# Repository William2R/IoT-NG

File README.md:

<h1 align="center">IndustrialSense</h1>
<p align="center">
  
  &nbsp; &nbsp; &nbsp; &nbsp;
  
</p>

***

## SPECIFICATIONS
| Parameter | Value | 
| --- | --- |
| **MCU** | ESP32-S3 |
| **LoRa Module** | Ra-01SH (Semtech SX1262) |
| **External Connectivity** | RS-485 / I2C / UART |
| **Expansion Support** | LTE A7680C (External Module via Headers) |
| **Dimensions** | 46.9 × 90.0 mm |

***

## DIRECTORY STRUCTURE

    .
    ├─ Computations       # Misc calculations
    ├─ HTML               # HTML files for generated webpage
    ├─ Images             # Pictures and renders
    │
    ├─ kibot_resources    # External resources for KiBot
    │  ├─ colors          # Color theme for KiCad
    │  ├─ fonts           # Fonts used in the project
    │  ├─ scripts         # External scripts used with KiBot
    │  └─ templates       # Templates for KiBot generated reports
    │
    ├─ kibot_yaml         # KiBot YAML config files
    ├─ KiRI               # KiRI (PCB diff viewer) files
    │
    ├─ lib                # KiCad footprint and symbol libraries
    │  ├─ 3d_models       # Component 3D models
    │  ├─ lib_fp          # Footprint libraries
    │  └─ lib_sym         # Symbol libraries
    │
    ├─ Logos              # Logos
    │
    ├─ Manufacturing      # Assembly and fabrication documents
    │  ├─ Assembly        # Assembly documents (BoM, pos, notes)
    │  │
    │  └─ Fabrication     # Fabrication documents (ZIP, notes)
    │     ├─ Drill Tables # CSV drill tables
    │     └─ Gerbers      # Gerbers
    │
    ├─ Report             # Reports for ERC/DRC
    ├─ Schematic          # PDF of schematic
    ├─ Templates          # Title block templates
    ├─ Testing
    │  └─ Testpoints      # Testpoints tables      
    │
    └─ Variants           # Outputs for assembly variants

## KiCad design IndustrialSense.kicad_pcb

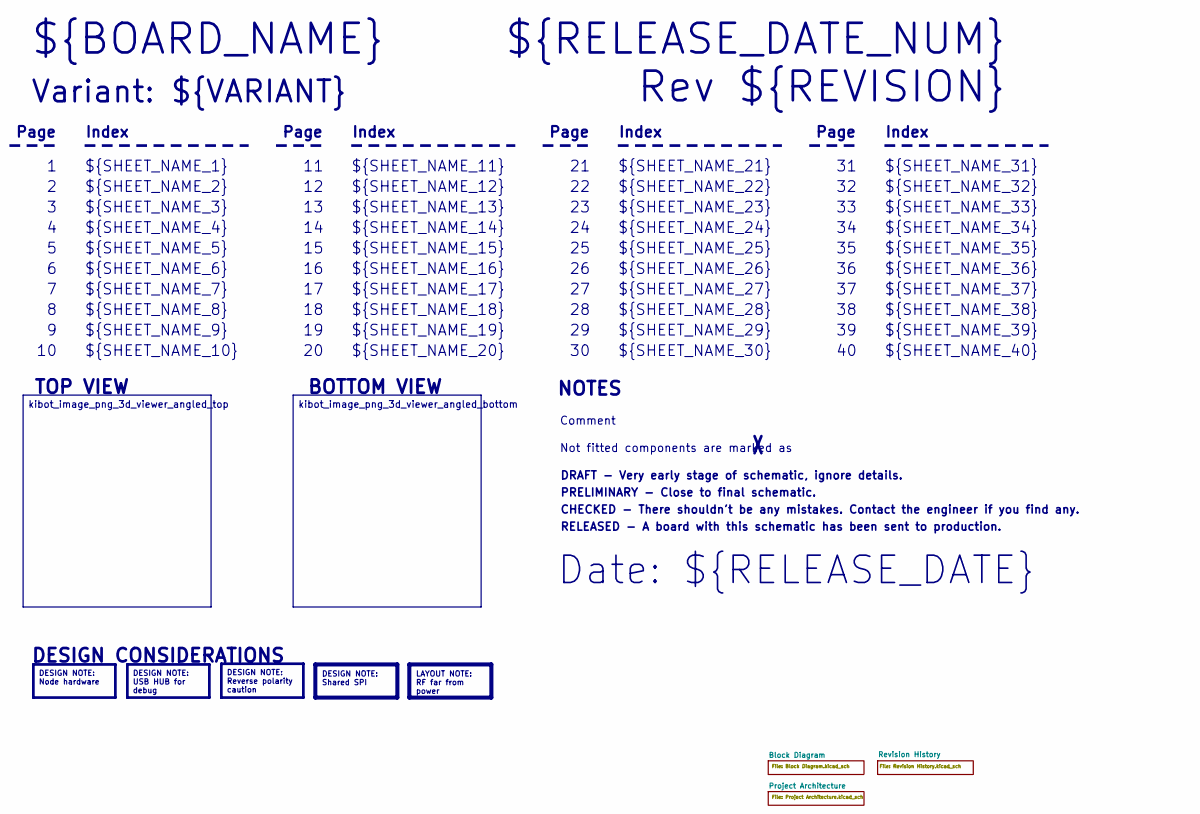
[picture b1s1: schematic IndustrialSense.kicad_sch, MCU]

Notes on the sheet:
Variant: ${VARIANT}
RELEASED - A board with this schematic has been sent to production.
${SHEET_NAME_24}
Index
Page
PRELIMINARY - Close to final schematic.
${SHEET_NAME_22}
DRAFT - Very early stage of schematic, ignore details.
${SHEET_NAME_12}
${SHEET_NAME_8}
${SHEET_NAME_2}
${SHEET_NAME_5}
${SHEET_NAME_20}
${SHEET_NAME_23}
${RELEASE_DATE_NUM}
${SHEET_NAME_35}
Not fitted components are marked as
${SHEET_NAME_11}
${SHEET_NAME_6}
${SHEET_NAME_37}
${SHEET_NAME_26}
${SHEET_NAME_36}
Rev ${REVISION}
${SHEET_NAME_15}
CHECKED - There shouldn't be any mistakes. Contact the engineer if you find any.
BOTTOM VIEW
${SHEET_NAME_14}
${SHEET_NAME_21}
${SHEET_NAME_17}
${SHEET_NAME_18}
Date: ${RELEASE_DATE}
${SHEET_NAME_7}
${SHEET_NAME_31}
${BOARD_NAME}
NOTES
${SHEET_NAME_40}
${SHEET_NAME_39}
${SHEET_NAME_32}
${SHEET_NAME_1}
${SHEET_NAME_9}

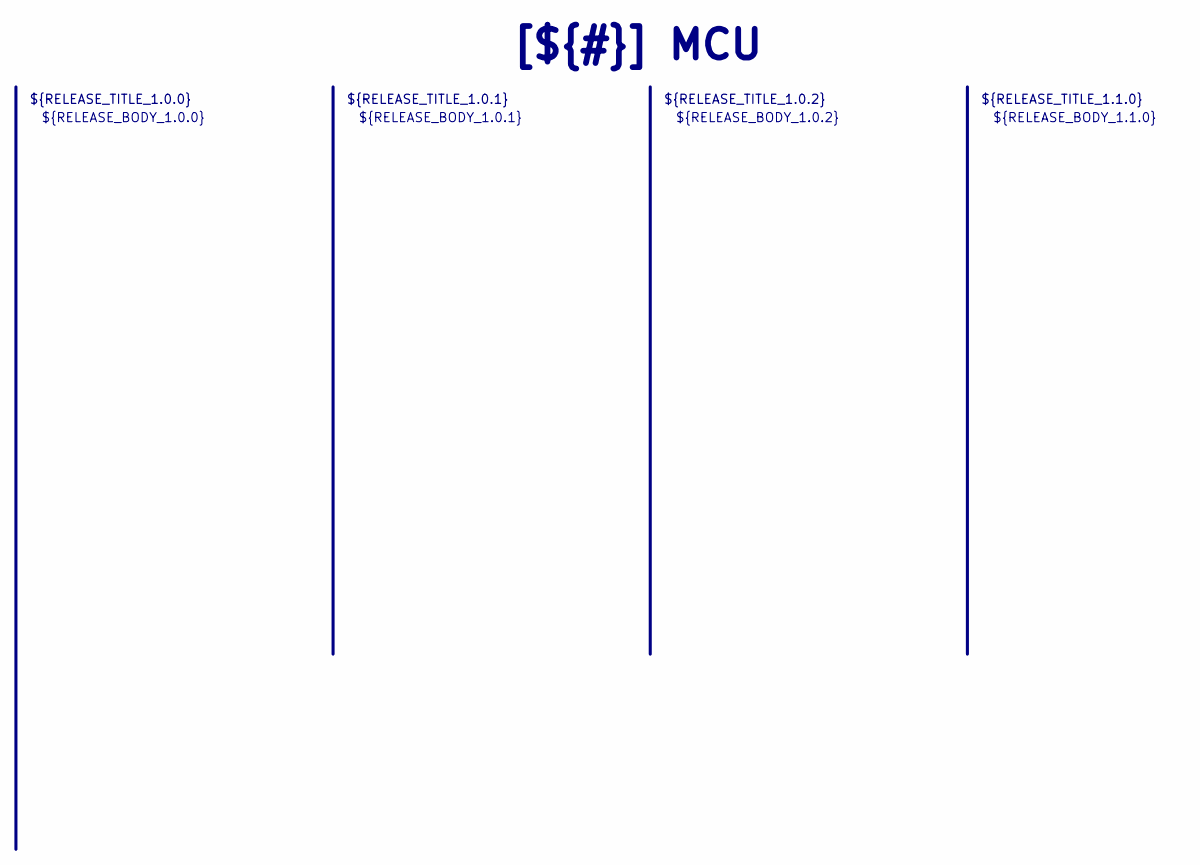
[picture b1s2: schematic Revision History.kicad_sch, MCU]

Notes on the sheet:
${RELEASE_BODY_1.1.0}
[${#}] ${TITLE}
${RELEASE_BODY_1.0.0}
${RELEASE_TITLE_1.0.2}
${RELEASE_BODY_1.0.2}
${RELEASE_BODY_1.0.1}
${RELEASE_TITLE_1.0.0}
${RELEASE_TITLE_1.0.1}
${RELEASE_TITLE_1.1.0}

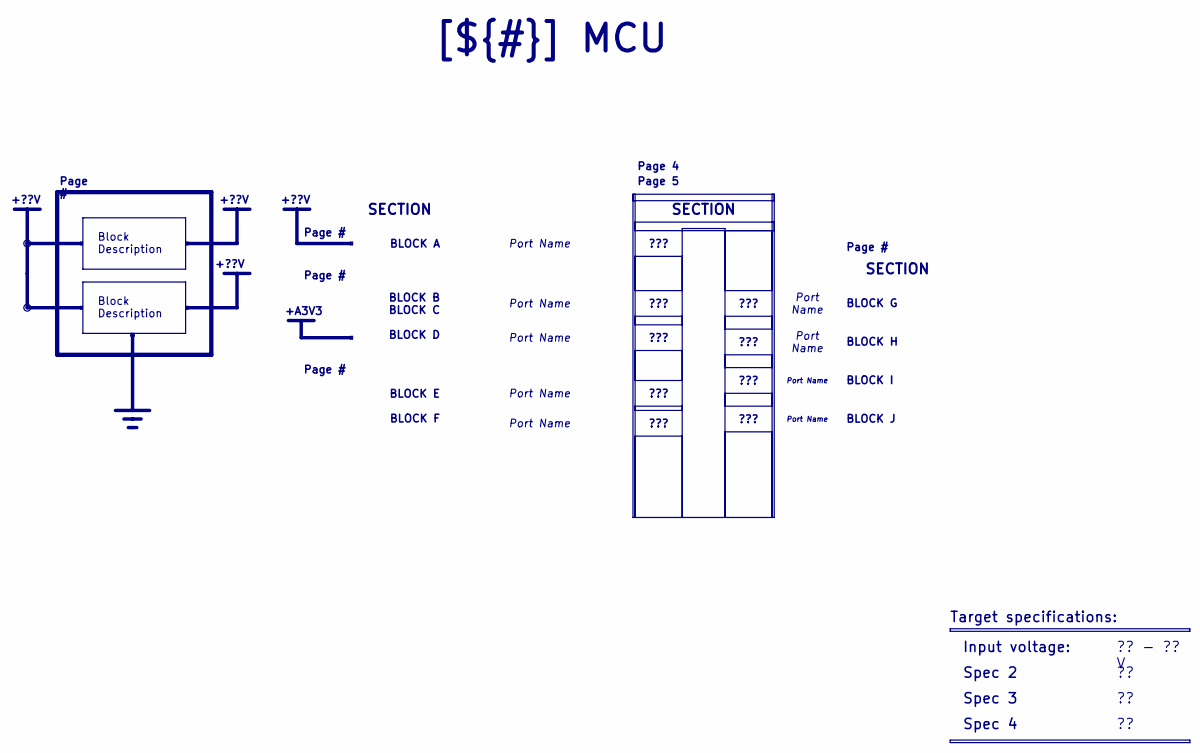
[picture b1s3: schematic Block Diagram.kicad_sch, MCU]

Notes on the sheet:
+??V
+A3V3
SECTION
Spec 4
BLOCK H
BLOCK B BLOCK C BLOCK D
BLOCK I
?? - ?? V
Block Description
???
Port Name
BLOCK G
Page #
Page 4
[${#}] ${TITLE}
Input voltage:
Target specifications:
Spec 3
Spec 2
BLOCK A
BLOCK E BLOCK F
BLOCK J
Page 5

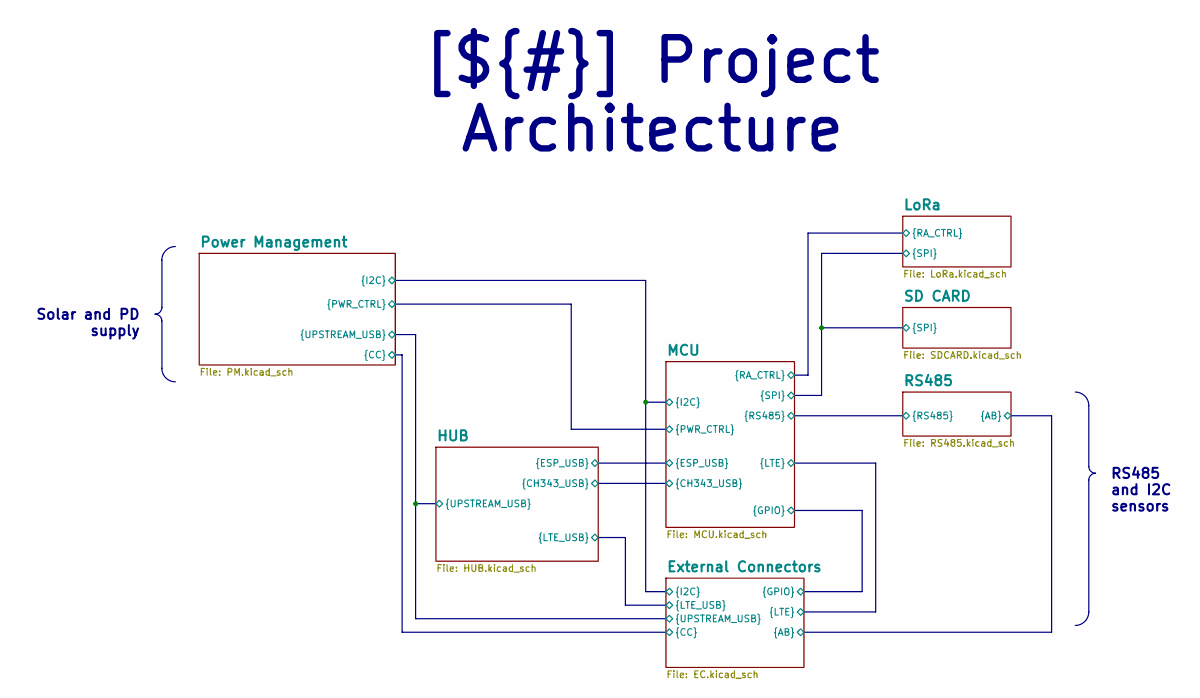
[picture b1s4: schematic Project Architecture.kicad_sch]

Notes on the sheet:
RS485 and I2C sensors
Solar and PD supply
[${#}] ${TITLE}

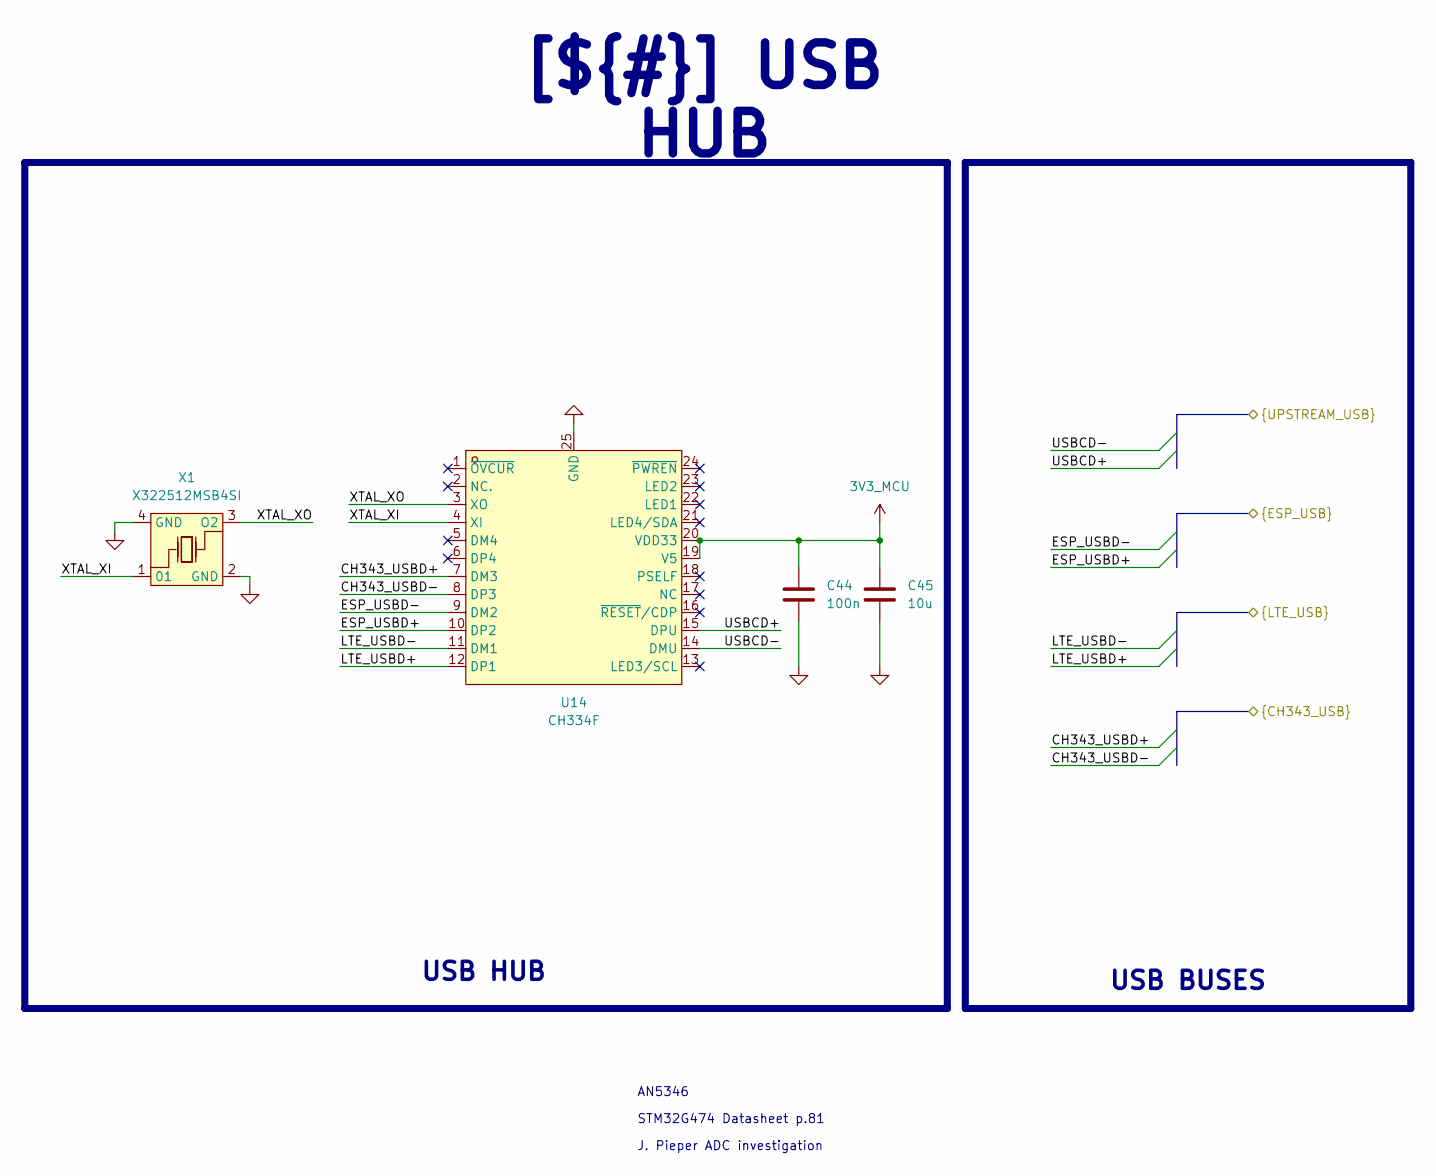
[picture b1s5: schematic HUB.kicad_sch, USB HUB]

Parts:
C44: 100n; C_0402_1005Metric; LCSC C77020
C45: 10u; C_0402_1005Metric; LCSC C77000
U14: CH334F; QFN-24_L4.0-W4.0-P0.50-BL-EP2.8; LCSC Part C9900029063
X1: X322512MSB4SI; CRYSTAL-SMD_4P-L3.2-W2.5-BL; LCSC Part C9002

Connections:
3V3_MCU: C44.1, C45.1, U14.19 (V5), U14.20 (VDD33); also elsewhere on the board
/Project Architecture/External Connectors/LTE_USBD+: U14.12 (DP1); also elsewhere on the board
/Project Architecture/External Connectors/LTE_USBD-: U14.11 (DM1); also elsewhere on the board
/Project Architecture/External Connectors/USBCD+: U14.15 (DPU); also elsewhere on the board
/Project Architecture/External Connectors/USBCD-: U14.14 (DMU); also elsewhere on the board
/Project Architecture/HUB/CH343_USBD+: U14.7 (DM3); also elsewhere on the board
/Project Architecture/HUB/CH343_USBD-: U14.8 (DP3); also elsewhere on the board
/Project Architecture/HUB/ESP_USBD+: U14.10 (DP2); also elsewhere on the board
/Project Architecture/HUB/ESP_USBD-: U14.9 (DM2); also elsewhere on the board
/Project Architecture/HUB/XTAL_XI: U14.4 (XI), X1.1
/Project Architecture/HUB/XTAL_XO: U14.3 (XO), X1.3 (O2)
GND: C44.2, C45.2, U14.25 (GND), X1.2 (GND), X1.4 (GND); also elsewhere on the board

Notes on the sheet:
J. Pieper ADC investigation
STM32G474 Datasheet p.81
AN5346
[${#}] ${TITLE}
USB HUB
USB BUSES

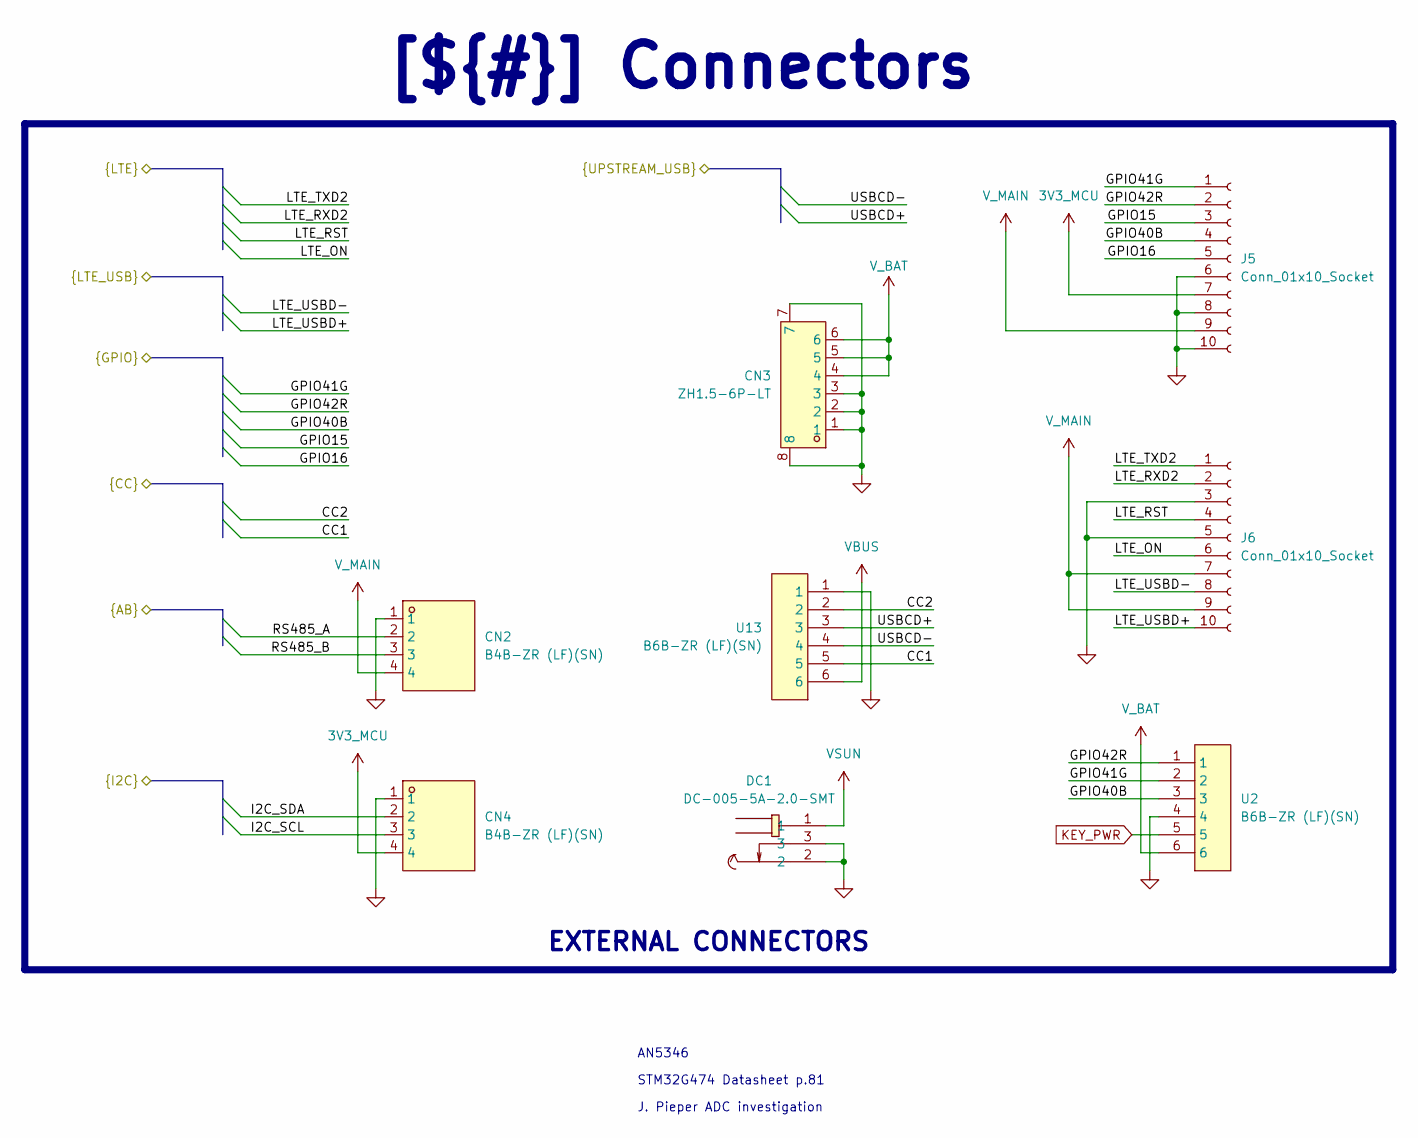
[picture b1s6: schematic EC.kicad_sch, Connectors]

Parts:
CN2, CN4: B4B-ZR (LF)(SN); CONN-TH_B4B-ZR-LF-SN; LCSC Part C157997
CN3: ZH1.5-6P-LT; CONN-SMD_ZH1.5-6P-LT; LCSC Part C722928
DC1: DC-005-5A-2.0-SMT; DC-IN-TH_DC-005-5A-2.0-SMT; LCSC Part C319134
J5, J6: Conn_01x10_Socket; PinHeader_2x05_P2.54mm_Vertical; LCSC C225520
U2, U13: B6B-ZR (LF)(SN); CONN-TH-6P-P1.50_B6B-ZR-LF-SN; LCSC Part C157984

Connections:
3V3_MCU: CN4.4, J5.7; also elsewhere on the board
/Project Architecture/External Connectors/CC1: U13.5; also elsewhere on the board
/Project Architecture/External Connectors/CC2: U13.2; also elsewhere on the board
/Project Architecture/External Connectors/GPIO15: J5.3; also elsewhere on the board
/Project Architecture/External Connectors/GPIO16: J5.5; also elsewhere on the board
/Project Architecture/External Connectors/GPIO40B: J5.4, U2.3; also elsewhere on the board
/Project Architecture/External Connectors/GPIO41G: J5.1, U2.2; also elsewhere on the board
/Project Architecture/External Connectors/GPIO42R: J5.2, U2.1; also elsewhere on the board
/Project Architecture/External Connectors/I2C_SCL: CN4.3; also elsewhere on the board
/Project Architecture/External Connectors/I2C_SDA: CN4.2; also elsewhere on the board
/Project Architecture/External Connectors/LTE_ON: J6.6; also elsewhere on the board
/Project Architecture/External Connectors/LTE_RST: J6.4; also elsewhere on the board
/Project Architecture/External Connectors/LTE_RXD2: J6.2; also elsewhere on the board
/Project Architecture/External Connectors/LTE_TXD2: J6.1; also elsewhere on the board
/Project Architecture/External Connectors/LTE_USBD+: J6.10; also elsewhere on the board
/Project Architecture/External Connectors/LTE_USBD-: J6.8; also elsewhere on the board
/Project Architecture/External Connectors/RS485_A: CN2.2; also elsewhere on the board
/Project Architecture/External Connectors/RS485_B: CN2.3; also elsewhere on the board
/Project Architecture/External Connectors/USBCD+: U13.3; also elsewhere on the board
/Project Architecture/External Connectors/USBCD-: U13.4; also elsewhere on the board
GND: CN2.1, CN3.1, CN3.2, CN3.3, CN3.7, CN3.8, CN4.1, DC1.2, DC1.3, J5.6, J5.8, J5.10, J6.3, J6.5, U2.4, U13.1; also elsewhere on the board
KEY_PWR: U2.5; also elsewhere on the board
VBUS: U13.6; also elsewhere on the board
VSUN: DC1.1; also elsewhere on the board
V_BAT: CN3.4, CN3.5, CN3.6, U2.6; also elsewhere on the board
V_MAIN: CN2.4, J5.9, J6.7, J6.9; also elsewhere on the board

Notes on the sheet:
J. Pieper ADC investigation
STM32G474 Datasheet p.81
AN5346
[${#}] ${TITLE}
EXTERNAL CONNECTORS

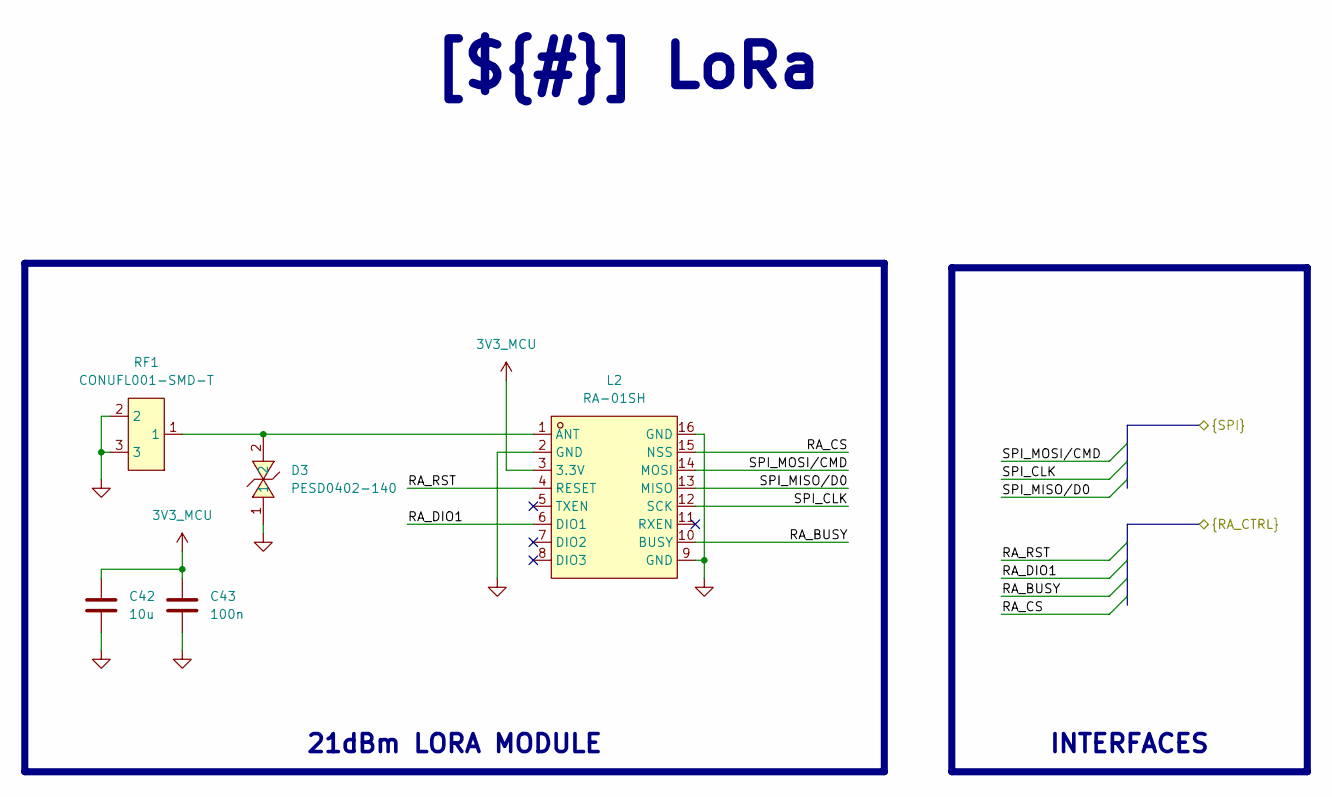
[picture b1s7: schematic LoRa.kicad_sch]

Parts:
C42: 10u; C_0603_1608Metric; LCSC C96446
C43: 100n; C_0603_1608Metric; LCSC C14663
D3: PESD0402-140; D0402-BI; LCSC Part C10662
L2: RA-01SH; WIRELM-SMD_RA-01SH; LCSC Part C2764087
RF1: CONUFL001-SMD-T; IPEX-SMD_3P-L2.6-W2.6-LS3.0; LCSC Part C22418213

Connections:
3V3_MCU: C42.1, C43.2, L2.3 (3.3V); also elsewhere on the board
/Project Architecture/LoRa/RA_BUSY: L2.10 (BUSY); also elsewhere on the board
/Project Architecture/LoRa/RA_CS: L2.15 (NSS); also elsewhere on the board
/Project Architecture/LoRa/RA_DIO1: L2.6 (DIO1); also elsewhere on the board
/Project Architecture/LoRa/RA_RST: L2.4 (RESET); also elsewhere on the board
/Project Architecture/LoRa/SPI_CLK: L2.12 (SCK); also elsewhere on the board
/Project Architecture/LoRa/SPI_MISO/D0: L2.13 (MISO); also elsewhere on the board
/Project Architecture/LoRa/SPI_MOSI/CMD: L2.14 (MOSI); also elsewhere on the board
GND: C42.2, C43.1, D3.1, L2.2 (GND), L2.9 (GND), L2.16 (GND), RF1.2, RF1.3; also elsewhere on the board
unnamed: D3.2, L2.1 (ANT), RF1.1

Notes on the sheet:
[${#}] ${TITLE}
21dBm LORA MODULE
INTERFACES

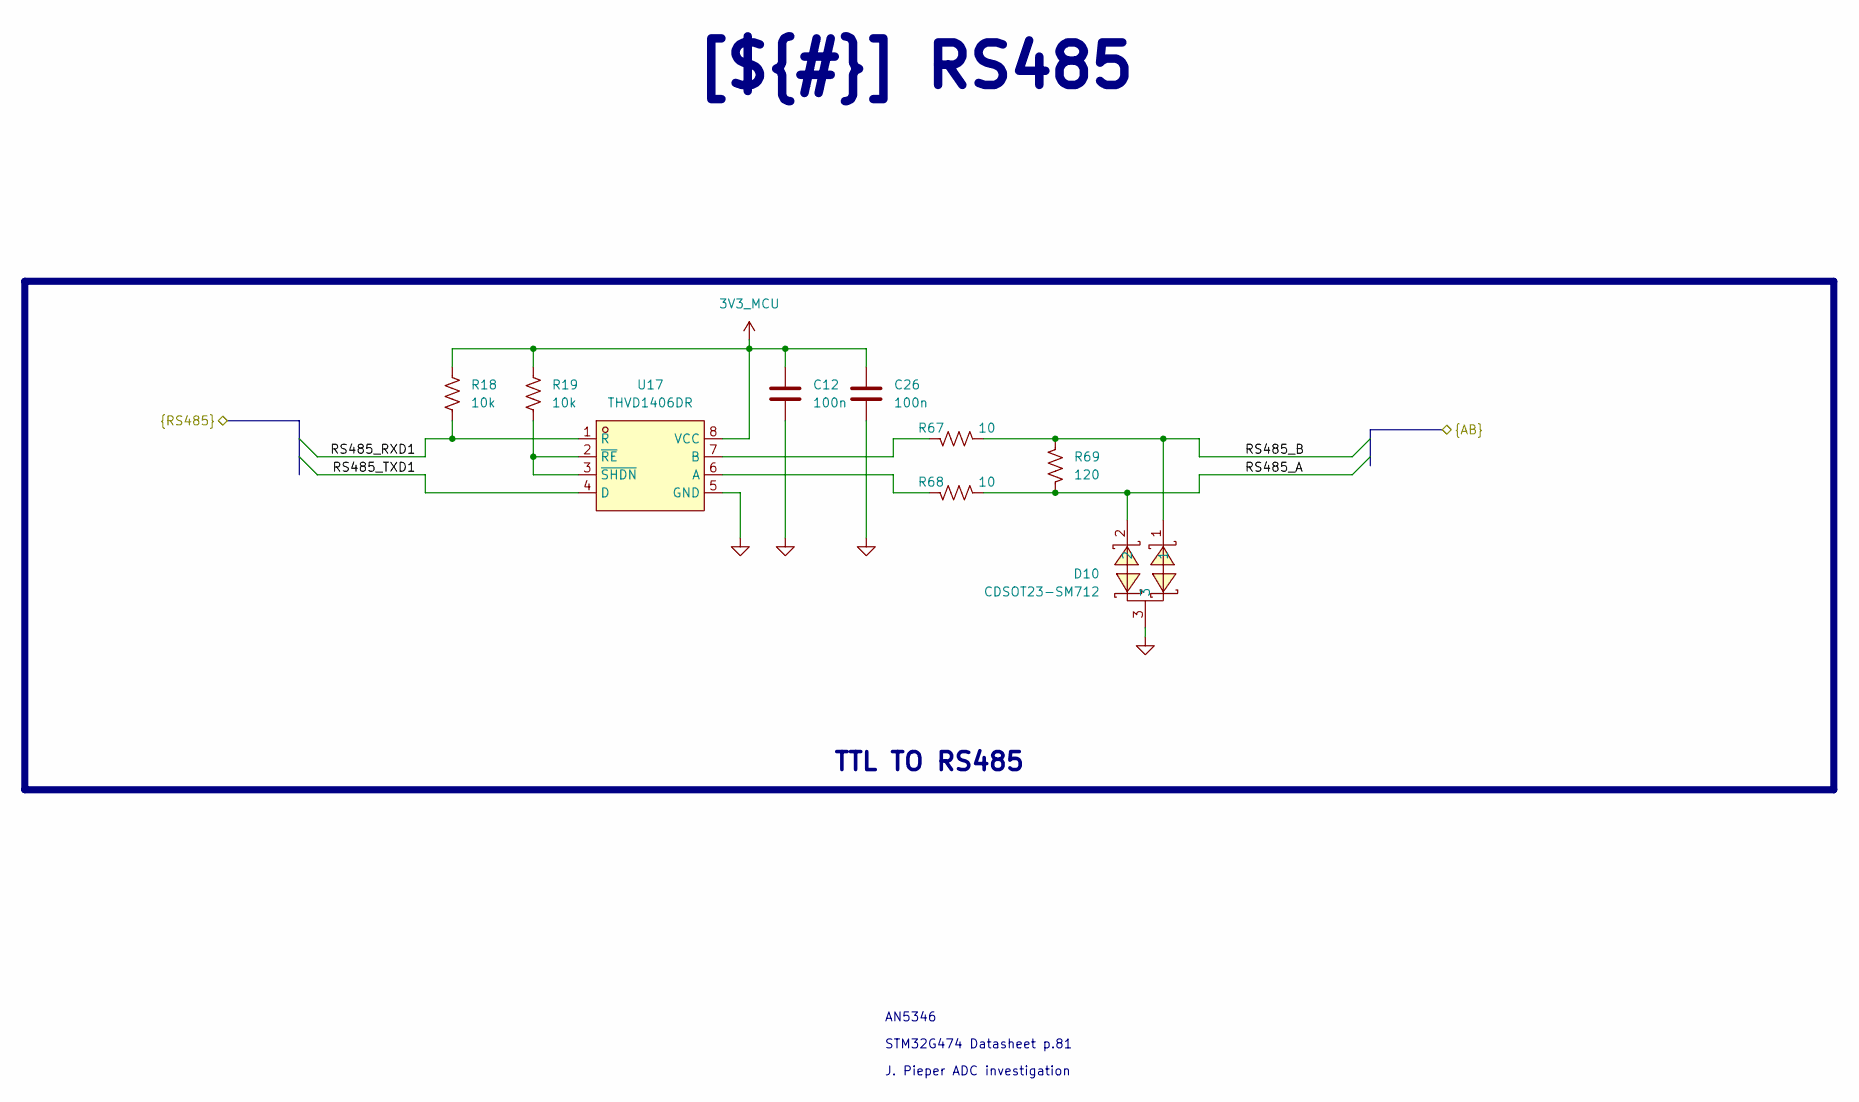
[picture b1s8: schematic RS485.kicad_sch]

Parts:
C12, C26: 100n; C_0402_1005Metric; LCSC C77020
D10: CDSOT23-SM712; SOT-23_L2.9-W1.3-P1.90-LS2.4-BR; LCSC Part C404012
R18, R19: 10k; R_0402_1005Metric; LCSC C25744
R67, R68: 10; R_0603_1608Metric; LCSC C313648
R69: 120; R_0603_1608Metric; LCSC C22787
U17: THVD1406DR; SOIC-8_L4.9-W3.9-P1.27-LS6.0-BL; LCSC Part C5215918

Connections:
3V3_MCU: C12.1, C26.1, R18.1, R19.1, U17.8 (VCC); also elsewhere on the board
/Project Architecture/External Connectors/RS485_A: D10.2, R68.2, R69.2; also elsewhere on the board
/Project Architecture/External Connectors/RS485_B: D10.1, R67.2, R69.1; also elsewhere on the board
/Project Architecture/MCU/RS485_RXD1: R18.2, U17.1 (R); also elsewhere on the board
/Project Architecture/MCU/RS485_TXD1: U17.4 (D); also elsewhere on the board
GND: C12.2, C26.2, D10.3, U17.5 (GND); also elsewhere on the board
unnamed: R68.1, U17.6 (A)
unnamed: R67.1, U17.7 (B)
unnamed: R19.2, U17.2 (~RE), U17.3 (~SHDN)

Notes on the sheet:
J. Pieper ADC investigation
STM32G474 Datasheet p.81
AN5346
TTL TO RS485
[${#}] ${TITLE}

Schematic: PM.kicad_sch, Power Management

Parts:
C1, C7: 47u; CAP-SMD_BD6.3-L6.6-W6.6-LS7.6-FD; LCSC Part C72523
C4, C6: 100u; C_1210_3225Metric; LCSC C394395
C5, C15, C17, C18, C19, C20, C22, C24: 100n; C_0402_1005Metric; LCSC C77020
C13: 22u; C_0805_2012Metric; LCSC C77071
C14, C21, C23: 10u; C_1210_3225Metric; LCSC C77100
C16: 3.3n; C_0603_1608Metric; LCSC C1613
C25: 220n; C_0402_1005Metric; LCSC C47129
C37, C38, C39: 1u; C_0402_1005Metric; LCSC C1518208
D1, D2: SS24; D_SMA; LCSC C50645
D4: BV24C; SOD-323_L1.7-W1.3-LS2.6-BI; LCSC Part C41419046
D5: DT1042-04SO-7; SOT-26_L3.0-W1.6-P0.95-LS2.8-BL; LCSC Part C460064
D6, D7, D8: 1N5819WS; D_SOD-323; LCSC C191023
D16: WHITE2; LED_0603_1608Metric; LCSC C2290
L3: XAL6060-223MEC; IND-SMD_L6.6-W6.4; LCSC Part C5366013
Q1, Q2, Q3, Q4: SISA14DN-T1-GE3; POWERPAK-1212-8_L3.3-W3.1-P0.65-BL-EP; LCSC Part C727488
Q5: CEM4435A; SO-8_L4.9-W3.9-P1.27-LS5.9-BL; LCSC Part C709930
Q6: CH221K; SOT-23-6_L2.9-W1.6-P0.95-LS2.8-BL-2; LCSC Part C5125736
Q13: MMBT3904; SOT-23; LCSC C20526
R1, R2, R3, R6: 1M; R_0402_1005Metric; LCSC C26083
R4, R5: 5.1k; R_0402_1005Metric; LCSC C25905
R7: 120; R_0402_1005Metric; LCSC C25079
R8: 50m; RES-SMD_L6.4-W3.2-R2512; LCSC Part C459687
R9: 820k; R_0402_1005Metric; LCSC C67558
R10: 100k; R_0402_1005Metric; LCSC C25741
R11, R60: 1k; R_0402_1005Metric; LCSC C11702
R12: 470k; R_0402_1005Metric; LCSC C25790
R13: 78.7k; R_0402_1005Metric; LCSC C67239
R47, R48: 47k; R_0603_1608Metric; LCSC C25819
R49, R56: 100k; R_0603_1608Metric; LCSC C25803
R55: 150k; R_0603_1608Metric; LCSC C22807
R59: 47k; R_0402_1005Metric; LCSC C25792
SW2: SKRKAEE020; SW-SMD_L3.9-W3.0-P4.45; LCSC Part C115357
TP1, TP2, TP3, TP4, TP5, TP6, TP7, TP8, TP9, TP10: TestPoint; tp05
U4: MAX17049G+T10; WSON-8_L2.0-W2.0-P0.50-BL-EP0.9; LCSC Part C18185545
U5, U6, U8, U10: LM74700QDBVRQ1; SOT-23-6_L2.9-W1.6-P0.95-LS2.8-BL; LCSC Part C2941042
U7: TPS62132RGTT; VQFN-16_L3.0-W3.0-P0.50-TL-EP; LCSC Part C2070674
U9: XC6209F332MR-G; SOT-25-5_L3.0-W1.8-P0.95-LS3.0-BR; LCSC Part C216624
U11: CN3795; SSOP-10_L4.9-W3.9-P1.00-LS6.0-BL; LCSC Part C150555
U12: XFL4020-222MEC_C122469; IND-SMD_L4.0-W4.0_XAL4030-332MEC; LCSC Part C122469
USB1: TYPE-C 16PIN 2MD(073); USB-C-SMD_TYPE-C-6PIN-2MD-073; LCSC Part C2765186

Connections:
3V3_FG: C38.1, TP2.1, U4.3 (VDD), U9.5 (VOUT)
3V3_MCU: C13.1, R49.1, TP4.1, U7.14 (VOS), U12.2; also elsewhere on the board
/Project Architecture/External Connectors/CC1: Q6.4 (CC1), R4.1, USB1.4 (CC1); also elsewhere on the board
/Project Architecture/External Connectors/CC2: Q6.5 (CC2), R5.1, USB1.10 (CC2); also elsewhere on the board
/Project Architecture/External Connectors/I2C_SCL: U4.7 (SCL); also elsewhere on the board
/Project Architecture/External Connectors/I2C_SDA: U4.8 (SDA); also elsewhere on the board
/Project Architecture/External Connectors/USBCD+: D5.3 (I/O2), USB1.6 (DP1), USB1.8 (DP2); also elsewhere on the board
/Project Architecture/External Connectors/USBCD-: D5.1 (I/O1), USB1.5 (DN2), USB1.7 (DN1); also elsewhere on the board
/Project Architecture/MCU/LOCK_PWR: D8.2 (A); also elsewhere on the board
/Project Architecture/MCU/PWR_KEY: Q13.3 (C), R49.2, TP8.1; also elsewhere on the board
/Project Architecture/Power Management/PWR_EN: R55.2, R56.1, TP10.1, U7.13 (EN)
/Project Architecture/Power Management/PWR_SEL: D6.1 (K), D7.1 (K), D8.1 (K), R55.1, TP9.1
GND: C1.2, C4.2, C5.2, C6.2, C7.2, C13.2, C14.2, C15.2, C16.2, C21.2, C22.2, C23.2, C25.2, C37.2, C38.2, C39.2, D1.2 (A), D4.1, D5.2 (VSS), Q6.2 (GND), Q13.2 (E), R4.2, R5.2, R10.2, R13.2, R47.2, R56.2, U4.1 (CTG), U4.4 (GND), U4.9 (GND), U5.2 (GND), U6.2 (GND), U7.5 (FB), U7.6 (AGND), U7.7 (FSW), U7.8 (DEF), U7.15 (PGND), U7.16 (PGND), U7.17 (EP), U8.2 (GND), U9.2 (VSS), U10.2 (GND), U11.2 (GND), USB1.1 (GND), USB1.12 (GND), USB1.13 (SHELL), USB1.14 (SHELL); also elsewhere on the board
KEY_PWR: D7.2 (A), R48.1, SW2.1; also elsewhere on the board
unnamed: C25.1, R7.2
unnamed: D1.1 (K), D2.1 (K), L3.1
unnamed: D2.2 (A), Q5.5 (D), Q5.6 (D), Q5.7 (D), Q5.8 (D)
unnamed: D16.2 (A), R11.2
unnamed: D16.1 (K), U11.3 (nCHRG)
unnamed: Q1.4 (G), R1.2, U5.5 (GATE)
unnamed: Q2.4 (G), R2.2, U6.5 (GATE)
unnamed: Q3.4 (G), R3.2, U8.5 (GATE)
unnamed: Q4.4 (G), R6.2, U10.5 (GATE)
unnamed: Q5.4 (G), U11.10 (DRV)
unnamed: Q6.6 (CFG), R59.2
unnamed: C37.1, Q6.1 (VDD), R59.1, R60.2
unnamed: Q13.1 (B), R47.1, R48.2
unnamed: C18.1, U5.1 (VCAP)
unnamed: C17.1, U6.1 (VCAP)
unnamed: C16.1, U7.9 (SS/TR)
unnamed: C19.1, U8.1 (VCAP)
unnamed: C20.1, U10.1 (VCAP)
unnamed: R7.1, U11.5 (COM)
unnamed: L3.2, R8.1, U11.8 (CSP)
unnamed: R12.2, R13.1, U11.6 (FB)
unnamed: R9.2, R10.1, U11.4 (MPPT)
unnamed: C24.1, U11.1 (VG)
unnamed: U7.1 (SW), U7.2 (SW), U7.3 (SW), U12.1
VBUS: C17.2, D4.2, D6.2 (A), Q2.1 (S), Q2.2 (S), Q2.3 (S), R2.1, R60.1, TP7.1, U6.3 (EN), U6.6 (ANODE), USB1.2 (VBUS), USB1.11 (VBUS); also elsewhere on the board
VSUN: C18.2, Q1.1 (S), Q1.2 (S), Q1.3 (S), R1.1, TP5.1, U5.3 (EN), U5.6 (ANODE); also elsewhere on the board
V_BAT: C5.1, C7.1, C20.2, C23.1, C39.1, Q4.1 (S), Q4.2 (S), Q4.3 (S), R6.1, R8.2, R12.1, SW2.2, TP3.1, U4.2 (CELL), U9.1 (VIN), U9.3 (CE), U10.3 (EN), U10.6 (ANODE), U11.7 (BAT); also elsewhere on the board
V_CHRG: C1.1, C19.2, C21.1, C22.1, C24.2, Q1.5 (D), Q1.6 (D), Q1.7 (D), Q1.8 (D), Q1.9 (D), Q2.5 (D), Q2.6 (D), Q2.7 (D), Q2.8 (D), Q2.9 (D), Q3.1 (S), Q3.2 (S), Q3.3 (S), Q5.1 (S), Q5.2 (S), Q5.3 (S), R3.1, R9.1, R11.1, TP6.1, U5.4 (CATHODE), U6.4 (CATHODE), U8.3 (EN), U8.6 (ANODE), U11.9 (VCC)
V_MAIN: C4.1, C6.1, C14.1, C15.1, Q3.5 (D), Q3.6 (D), Q3.7 (D), Q3.8 (D), Q3.9 (D), Q4.5 (D), Q4.6 (D), Q4.7 (D), Q4.8 (D), Q4.9 (D), TP1.1, U7.10 (AVIN), U7.11 (PVIN), U7.12 (PVIN), U8.4 (CATHODE), U10.4 (CATHODE); also elsewhere on the board

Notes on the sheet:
INPUT VOLTAGE O-RING
12V PD CONTROLLER
3.3V SUPPLY
TYPE C PORT
2S FUEL GAUGE
[${#}] ${TITLE}
2.4A CHARGER
INTERFACES
TESTPOINTS
BUTTON DETECTION
OUTPUT VOLTAGE O-RING

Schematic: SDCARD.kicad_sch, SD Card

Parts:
Card1: XKTF-0803-0; TF-SMD_XKTF-0803-0; LCSC Part C381083
R50: 100k; R_0603_1608Metric; LCSC C25803

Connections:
3V3_MCU: Card1.4 (VDD), R50.1; also elsewhere on the board
/Project Architecture/LoRa/SPI_CLK: Card1.5 (CLK); also elsewhere on the board
/Project Architecture/LoRa/SPI_MISO/D0: Card1.7 (DAT0); also elsewhere on the board
/Project Architecture/LoRa/SPI_MOSI/CMD: Card1.3 (CMD); also elsewhere on the board
GND: Card1.6 (VSS), Card1.10 (SHELL), Card1.11 (SHELL), Card1.12 (SHELL), Card1.13 (SHELL); also elsewhere on the board
SD_CS/D3: Card1.2 (CD/DAT3), R50.2; also elsewhere on the board

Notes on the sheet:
Flexible I/O worked examples
References:
Flexible I/O source configuration
[${#}] ${TITLE}
MICRO SD SLOT

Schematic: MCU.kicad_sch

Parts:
C40, C48: 100n; C_0603_1608Metric; LCSC C14663
C41: 10u; C_0603_1608Metric; LCSC C96446
C46, C47: 1u; C_0603_1608Metric; LCSC C15849
Q15: LMBT3904DW1T1G; SOT-363_L2.0-W1.3-P0.65-LS2.1-BR; LCSC Part C131781
R53, R54, R57, R58: 10k; R_0603_1608Metric; LCSC C25804
SW3: SKRKAEE020; SW-SMD_L3.9-W3.0-P4.45; LCSC Part C115357
U1: ESP32-S3-WROOM-1U-N16; WIRELM-SMD_ESP32-S3-WROOM-1U; LCSC Part C2980298
U3: CH343P; TQFN-16_L3.0-W3.0-P0.50-BL-EP1.7; LCSC Part C2846043
U15: TPS3831G33DQNR; X2SON-4_L1.0-W1.0-P0.65-TL-EP; LCSC Part C2066649

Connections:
3V3_MCU: C40.2, C41.1, C47.1, R57.1, R58.1, U1.2 (3V3), U3.1 (VIO), U3.9 (VBUS), U15.4 (VDD); also elsewhere on the board
/Project Architecture/External Connectors/GPIO15: U1.8 (IO15); also elsewhere on the board
/Project Architecture/External Connectors/GPIO16: U1.9 (IO16); also elsewhere on the board
/Project Architecture/External Connectors/GPIO40B: U1.33 (IO40); also elsewhere on the board
/Project Architecture/External Connectors/GPIO41G: U1.34 (IO41); also elsewhere on the board
/Project Architecture/External Connectors/GPIO42R: U1.35 (IO42); also elsewhere on the board
/Project Architecture/External Connectors/I2C_SCL: R57.2, U1.17 (IO9); also elsewhere on the board
/Project Architecture/External Connectors/I2C_SDA: R58.2, U1.12 (IO8); also elsewhere on the board
/Project Architecture/External Connectors/LTE_ON: U1.7 (IO7); also elsewhere on the board
/Project Architecture/External Connectors/LTE_RST: U1.6 (IO6); also elsewhere on the board
/Project Architecture/External Connectors/LTE_RXD2: U1.5 (IO5); also elsewhere on the board
/Project Architecture/External Connectors/LTE_TXD2: U1.4 (IO4); also elsewhere on the board
/Project Architecture/HUB/CH343_USBD+: U3.7 (UD+); also elsewhere on the board
/Project Architecture/HUB/CH343_USBD-: U3.8 (UD-); also elsewhere on the board
/Project Architecture/HUB/ESP_USBD+: U1.14 (IO20); also elsewhere on the board
/Project Architecture/HUB/ESP_USBD-: U1.13; also elsewhere on the board
/Project Architecture/LoRa/RA_BUSY: U1.23 (IO21); also elsewhere on the board
/Project Architecture/LoRa/RA_CS: U1.22 (IO14); also elsewhere on the board
/Project Architecture/LoRa/RA_DIO1: U1.24 (25); also elsewhere on the board
/Project Architecture/LoRa/RA_RST: U1.25 (IO48); also elsewhere on the board
/Project Architecture/LoRa/SPI_CLK: U1.20 (IO12); also elsewhere on the board
/Project Architecture/LoRa/SPI_MISO/D0: U1.21 (IO13); also elsewhere on the board
/Project Architecture/LoRa/SPI_MOSI/CMD: U1.19 (IO11); also elsewhere on the board
/Project Architecture/MCU/CH343_DTR: Q15.1 (E), R53.1, U3.12 (DTRTNOW)
/Project Architecture/MCU/CH343_RTS: Q15.4 (E), R54.2, U3.13 (RTS)
/Project Architecture/MCU/ESP_BOOT: Q15.6 (C), U1.27 (IO0)
/Project Architecture/MCU/ESP_EN: Q15.3 (C), U1.3 (EN), U15.1 (~RESET)
/Project Architecture/MCU/ESP_RXD0: U1.36 (RXD0), U3.4 (TXD)
/Project Architecture/MCU/ESP_TXD0: U1.37 (TXD0), U3.5 (RXD)
/Project Architecture/MCU/LOCK_PWR: U1.32 (IO39); also elsewhere on the board
/Project Architecture/MCU/PWR_KEY: U1.31 (IO38); also elsewhere on the board
/Project Architecture/MCU/RS485_RXD1: U1.11 (IO18); also elsewhere on the board
/Project Architecture/MCU/RS485_TXD1: U1.10 (IO17); also elsewhere on the board
GND: C40.1, C41.2, C46.2, C47.2, C48.2, SW3.1, U1.1 (GND), U1.40 (GND), U1.41 (GND), U3.2 (GND), U3.17 (EP), U15.3 (GND), U15.5 (EP); also elsewhere on the board
unnamed: Q15.2 (B), R54.1
unnamed: Q15.5 (B), R53.2
unnamed: C46.1, C48.1, U3.3 (VDD5), U3.6 (V3)
unnamed: SW3.2, U15.2 (~MR)
SD_CS/D3: U1.18 (IO10); also elsewhere on the board

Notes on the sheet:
INTERFACES
[${#}] ${TITLE}
TTL TO USB
ESP32 S3
INTERFACES
